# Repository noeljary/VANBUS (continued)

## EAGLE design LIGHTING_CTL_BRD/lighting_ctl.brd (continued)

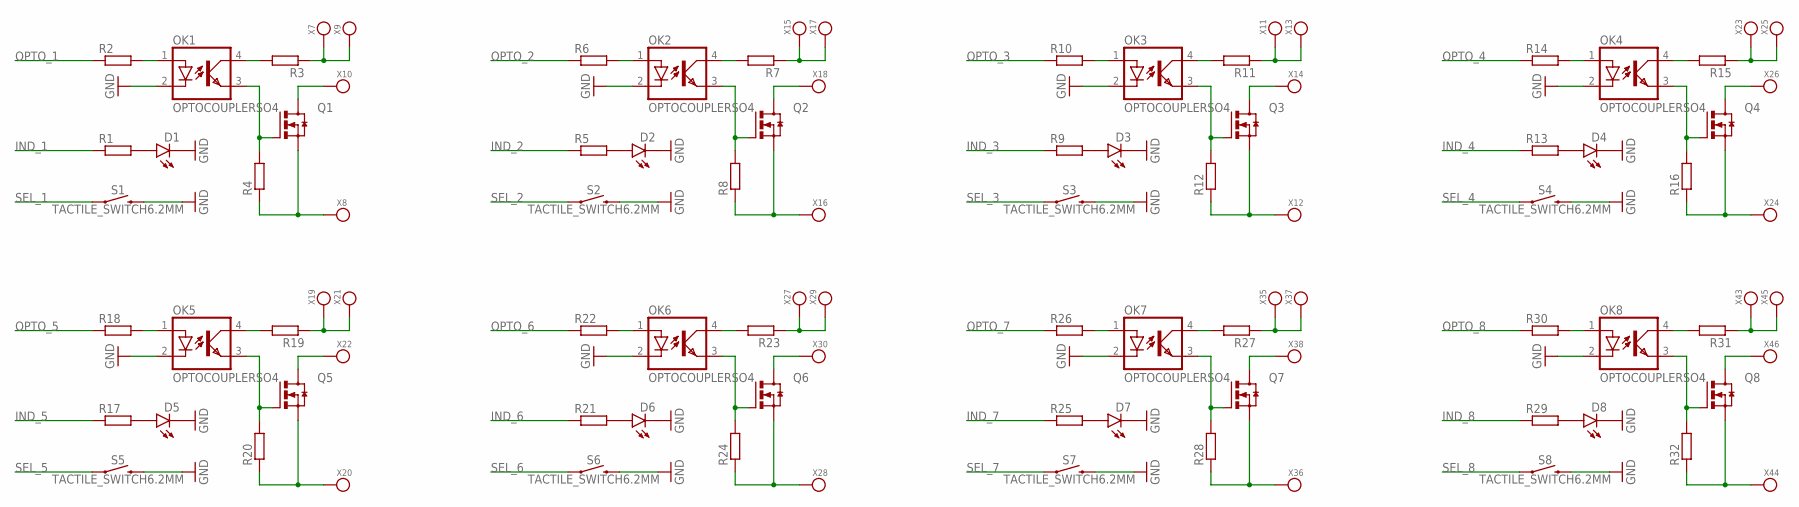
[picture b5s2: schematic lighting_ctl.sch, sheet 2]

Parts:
D1, D2, D3, D4, D5, D6, D7, D8: LED1206; CHIPLED_1206
OK1, OK2, OK3, OK4, OK5, OK6, OK7, OK8: OPTOCOUPLERSO4; SO04
Q1, Q2, Q3, Q4, Q5, Q6, Q7, Q8: MOSFET_N_CHANNELSOT223; SOT223
R1, R2, R3, R4, R5, R6, R7, R8, R9, R10, R11, R12, R13, R14, R15, R16, R17, R18, R19, R20, R21, R22, R23, R24, R25, R26, R27, R28, R29, R30, R31, R32: RESISTOR0805; R0805
S1, S2, S3, S4, S5, S6, S7, S8: TACTILE_SWITCH6.2MM; TACTILE_SWITCH_SMD_6.2MM
X7, X8, X9, X10, X11, X12, X13, X14, X15, X16, X17, X18, X19, X20, X21, X22, X23, X24, X25, X26, X27, X28, X29, X30, X35, X36, X37, X38, X43, X44, X45, X46: KEYSTONE_7788

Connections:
GND: D1.C, D2.C, D3.C, D4.C, D5.C, D6.C, D7.C, D8.C, OK1.2 (C), OK2.2 (C), OK3.2 (C), OK4.2 (C), OK5.2 (C), OK6.2 (C), OK7.2 (C), OK8.2 (C), S1.B1 (2), S1.B2 (2), S2.B1 (2), S2.B2 (2), S3.B1 (2), S3.B2 (2), S4.B1 (2), S4.B2 (2), S5.B1 (2), S5.B2 (2), S6.B1 (2), S6.B2 (2), S7.B1 (2), S7.B2 (2), S8.B1 (2), S8.B2 (2); also elsewhere on the board
IND_1: R1.1; also elsewhere on the board
IND_2: R5.1; also elsewhere on the board
IND_3: R9.1; also elsewhere on the board
IND_4: R13.1; also elsewhere on the board
IND_5: R17.1; also elsewhere on the board
IND_6: R21.1; also elsewhere on the board
IND_7: R25.1; also elsewhere on the board
IND_8: R29.1; also elsewhere on the board
unnamed: OK1.1 (A), R2.2
unnamed: D1.A, R1.2
unnamed: OK1.4 (COL), R3.2
unnamed: R3.1, X7.1, X7.2, X7.3, X7.4, X9.1, X9.2, X9.3, X9.4
unnamed: Q1.2 (D), Q1.4 (D), X10.1, X10.2, X10.3, X10.4
unnamed: OK1.3 (EMIT), Q1.1 (G), R4.2
unnamed: Q1.3 (S), R4.1, X8.1, X8.2, X8.3, X8.4
unnamed: OK3.1 (A), R10.2
unnamed: D3.A, R9.2
unnamed: OK3.4 (COL), R11.2
unnamed: R11.1, X11.1, X11.2, X11.3, X11.4, X13.1, X13.2, X13.3, X13.4
unnamed: Q3.2 (D), Q3.4 (D), X14.1, X14.2, X14.3, X14.4
unnamed: OK3.3 (EMIT), Q3.1 (G), R12.2
unnamed: Q3.3 (S), R12.1, X12.1, X12.2, X12.3, X12.4
unnamed: OK2.1 (A), R6.2
unnamed: D2.A, R5.2
unnamed: OK2.4 (COL), R7.2
unnamed: R7.1, X15.1, X15.2, X15.3, X15.4, X17.1, X17.2, X17.3, X17.4
unnamed: Q2.2 (D), Q2.4 (D), X18.1, X18.2, X18.3, X18.4
unnamed: OK2.3 (EMIT), Q2.1 (G), R8.2
unnamed: Q2.3 (S), R8.1, X16.1, X16.2, X16.3, X16.4
unnamed: OK5.1 (A), R18.2
unnamed: D5.A, R17.2
unnamed: OK5.4 (COL), R19.2
unnamed: R19.1, X19.1, X19.2, X19.3, X19.4, X21.1, X21.2, X21.3, X21.4
unnamed: Q5.2 (D), Q5.4 (D), X22.1, X22.2, X22.3, X22.4
unnamed: OK5.3 (EMIT), Q5.1 (G), R20.2
unnamed: Q5.3 (S), R20.1, X20.1, X20.2, X20.3, X20.4
unnamed: OK4.1 (A), R14.2
unnamed: D4.A, R13.2
unnamed: OK4.4 (COL), R15.2
unnamed: R15.1, X23.1, X23.2, X23.3, X23.4, X25.1, X25.2, X25.3, X25.4
unnamed: Q4.2 (D), Q4.4 (D), X26.1, X26.2, X26.3, X26.4
unnamed: OK4.3 (EMIT), Q4.1 (G), R16.2
unnamed: Q4.3 (S), R16.1, X24.1, X24.2, X24.3, X24.4
unnamed: OK6.1 (A), R22.2
unnamed: D6.A, R21.2
unnamed: OK6.4 (COL), R23.2
unnamed: R23.1, X27.1, X27.2, X27.3, X27.4, X29.1, X29.2, X29.3, X29.4
unnamed: Q6.2 (D), Q6.4 (D), X30.1, X30.2, X30.3, X30.4
unnamed: OK6.3 (EMIT), Q6.1 (G), R24.2
unnamed: Q6.3 (S), R24.1, X28.1, X28.2, X28.3, X28.4
unnamed: OK7.1 (A), R26.2
unnamed: D7.A, R25.2
unnamed: OK7.4 (COL), R27.2
unnamed: R27.1, X35.1, X35.2, X35.3, X35.4, X37.1, X37.2, X37.3, X37.4
unnamed: Q7.2 (D), Q7.4 (D), X38.1, X38.2, X38.3, X38.4
unnamed: OK7.3 (EMIT), Q7.1 (G), R28.2
unnamed: Q7.3 (S), R28.1, X36.1, X36.2, X36.3, X36.4
unnamed: OK8.1 (A), R30.2
unnamed: D8.A, R29.2
unnamed: OK8.4 (COL), R31.2
unnamed: R31.1, X43.1, X43.2, X43.3, X43.4, X45.1, X45.2, X45.3, X45.4
unnamed: Q8.2 (D), Q8.4 (D), X46.1, X46.2, X46.3, X46.4
unnamed: OK8.3 (EMIT), Q8.1 (G), R32.2
unnamed: Q8.3 (S), R32.1, X44.1, X44.2, X44.3, X44.4
OPTO_1: R2.1; also elsewhere on the board
OPTO_2: R6.1; also elsewhere on the board
OPTO_3: R10.1; also elsewhere on the board
OPTO_4: R14.1; also elsewhere on the board
OPTO_5: R18.1; also elsewhere on the board
OPTO_6: R22.1; also elsewhere on the board
OPTO_7: R26.1; also elsewhere on the board
OPTO_8: R30.1; also elsewhere on the board
SEL_1: S1.A1 (1), S1.A2 (1); also elsewhere on the board
SEL_2: S2.A1 (1), S2.A2 (1); also elsewhere on the board
SEL_3: S3.A1 (1), S3.A2 (1); also elsewhere on the board
SEL_4: S4.A1 (1), S4.A2 (1); also elsewhere on the board
SEL_5: S5.A1 (1), S5.A2 (1); also elsewhere on the board
SEL_6: S6.A1 (1), S6.A2 (1); also elsewhere on the board
SEL_7: S7.A1 (1), S7.A2 (1); also elsewhere on the board
SEL_8: S8.A1 (1), S8.A2 (1); also elsewhere on the board

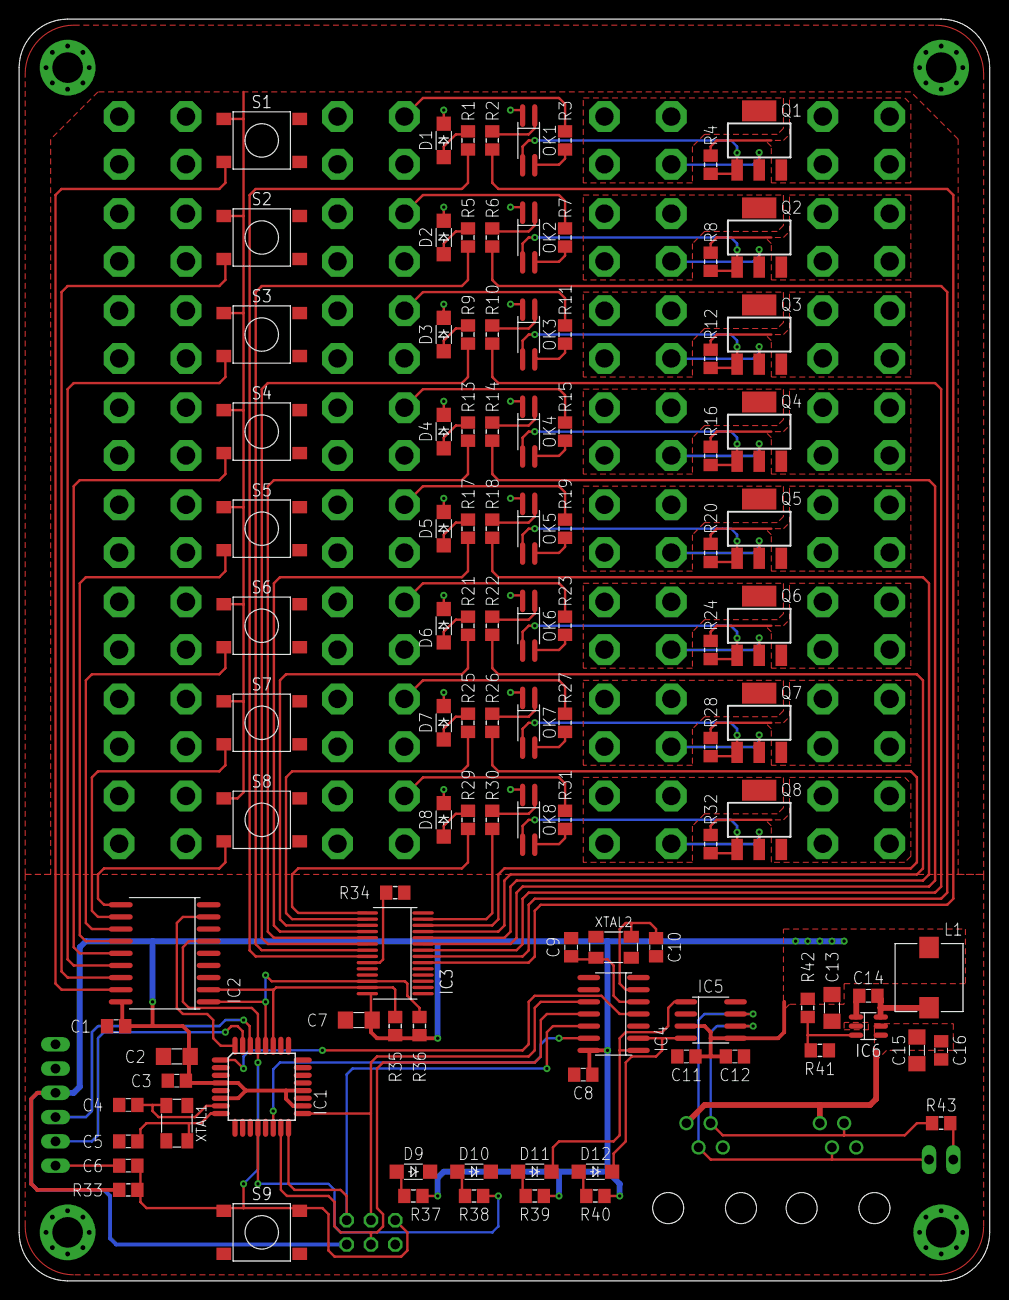
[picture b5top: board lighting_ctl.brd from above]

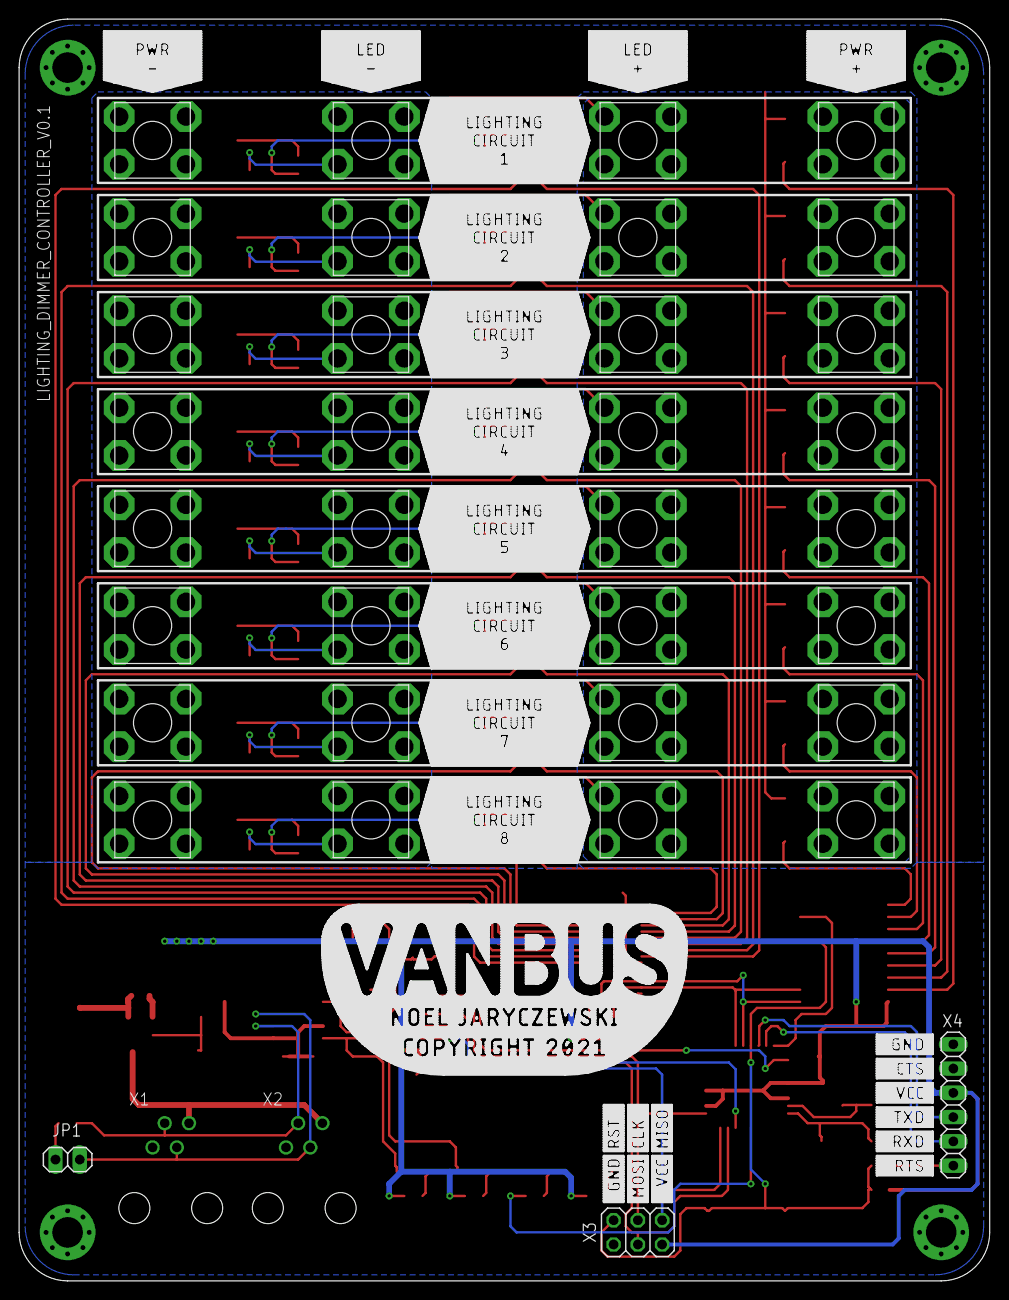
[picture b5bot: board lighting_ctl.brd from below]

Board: 2 copper layers, 101.6 x 132.1 mm, 146 parts (37 on the bottom side), 113 nets.

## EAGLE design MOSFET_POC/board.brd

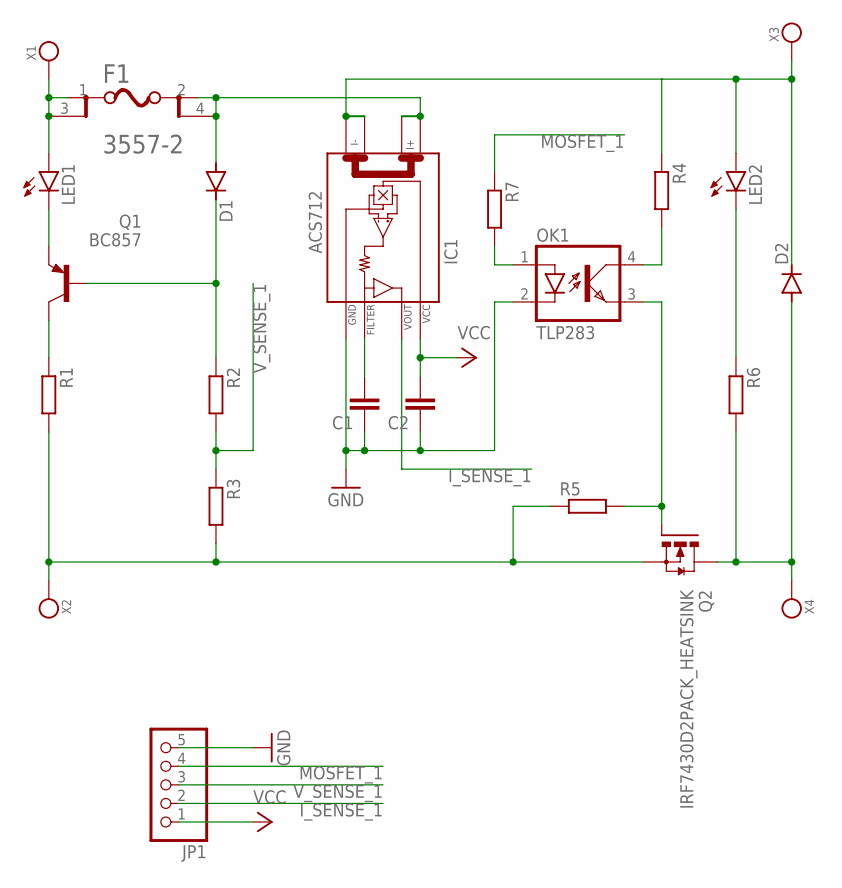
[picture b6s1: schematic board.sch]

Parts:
C1, C2: C-EUC0805; C0805
D1: DIODE-SOD123; DIODE_SOD123
D2: DIODE-DO214AC; DO214AC
F1: KEYSTONE_3557-2KEYSTONE_3557-2_0_0; KEYSTONE_3557-2_0
IC1: ACS712; SO08
JP1: PINHD-1X5; 1X05
LED1, LED2: LEDSMT1206; 1206
OK1: TLP283; MINI-FLAT-4
Q1: BC857; SOT23-BEC
Q2: IRF7430D2PACK_HEATSINK; D2PACK_HEATSINK
R1, R2, R3, R4, R5, R6, R7: R-EU_R0805; R0805
X1, X2, X3, X4: 7800

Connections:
GND: C1.1, C2.1, IC1.5 (GND), JP1.5, OK1.2 (C)
I_SENSE_1: IC1.7 (VOUT), JP1.2
MOSFET_1: JP1.4, R7.1
unnamed: F1.1, F1.3, LED1.A, X1.1, X1.2, X1.3, X1.4, X1.5, X1.6
unnamed: LED1.C, Q1.E
unnamed: Q1.C, R1.1
unnamed: Q2.3 (S), R1.2, R3.2, R5.1, X2.1, X2.2, X2.3, X2.4, X2.5, X2.6
unnamed: D2.C, IC1.3 (I-_0), IC1.4 (I-_1), LED2.A, R4.1, X3.1, X3.2, X3.3, X3.4, X3.5, X3.6
unnamed: LED2.C, R6.1
unnamed: D1.A, F1.2, F1.4, IC1.1 (I+_0), IC1.2 (I+_1)
unnamed: D1.C, Q1.B, R2.1
unnamed: C1.2, IC1.6 (FILTER)
unnamed: OK1.4 (COL), R4.2
unnamed: OK1.1 (A), R7.2
unnamed: OK1.3 (EMIT), Q2.1 (G), R5.2
unnamed: D2.A, Q2.2 (D), Q2.4 (D), Q2.5 (D), R6.2, X4.1, X4.2, X4.3, X4.4, X4.5, X4.6
VCC: C2.2, IC1.8 (VCC), JP1.1
V_SENSE_1: JP1.3, R2.2, R3.1

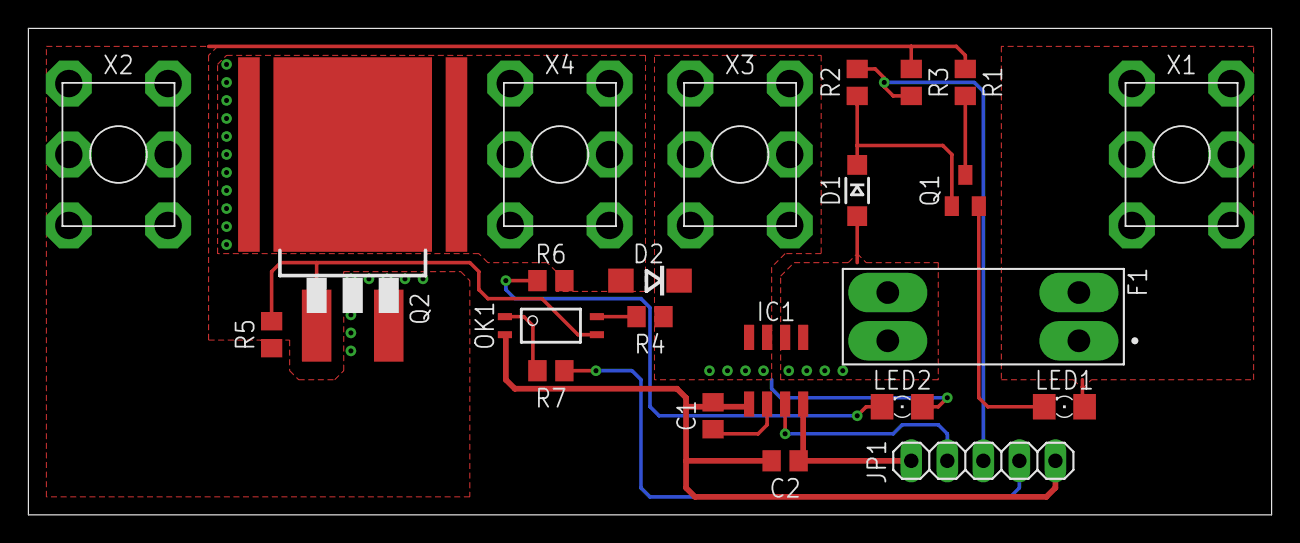
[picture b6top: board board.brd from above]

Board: 2 copper layers, 87.6 x 34.3 mm, 23 parts (0 on the bottom side), 18 nets.

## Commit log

2021-07-03 Initial load of VANBUS circuits
2021-07-12 Layout updates for MOSFET & LIGHTING boards. Add new boards REMOTE_SWITCH, CAPACITIVE_SWITCH, VANBUS_HUB
2021-07-13 v0.1 Production Run Commit - Including GERBER Files
